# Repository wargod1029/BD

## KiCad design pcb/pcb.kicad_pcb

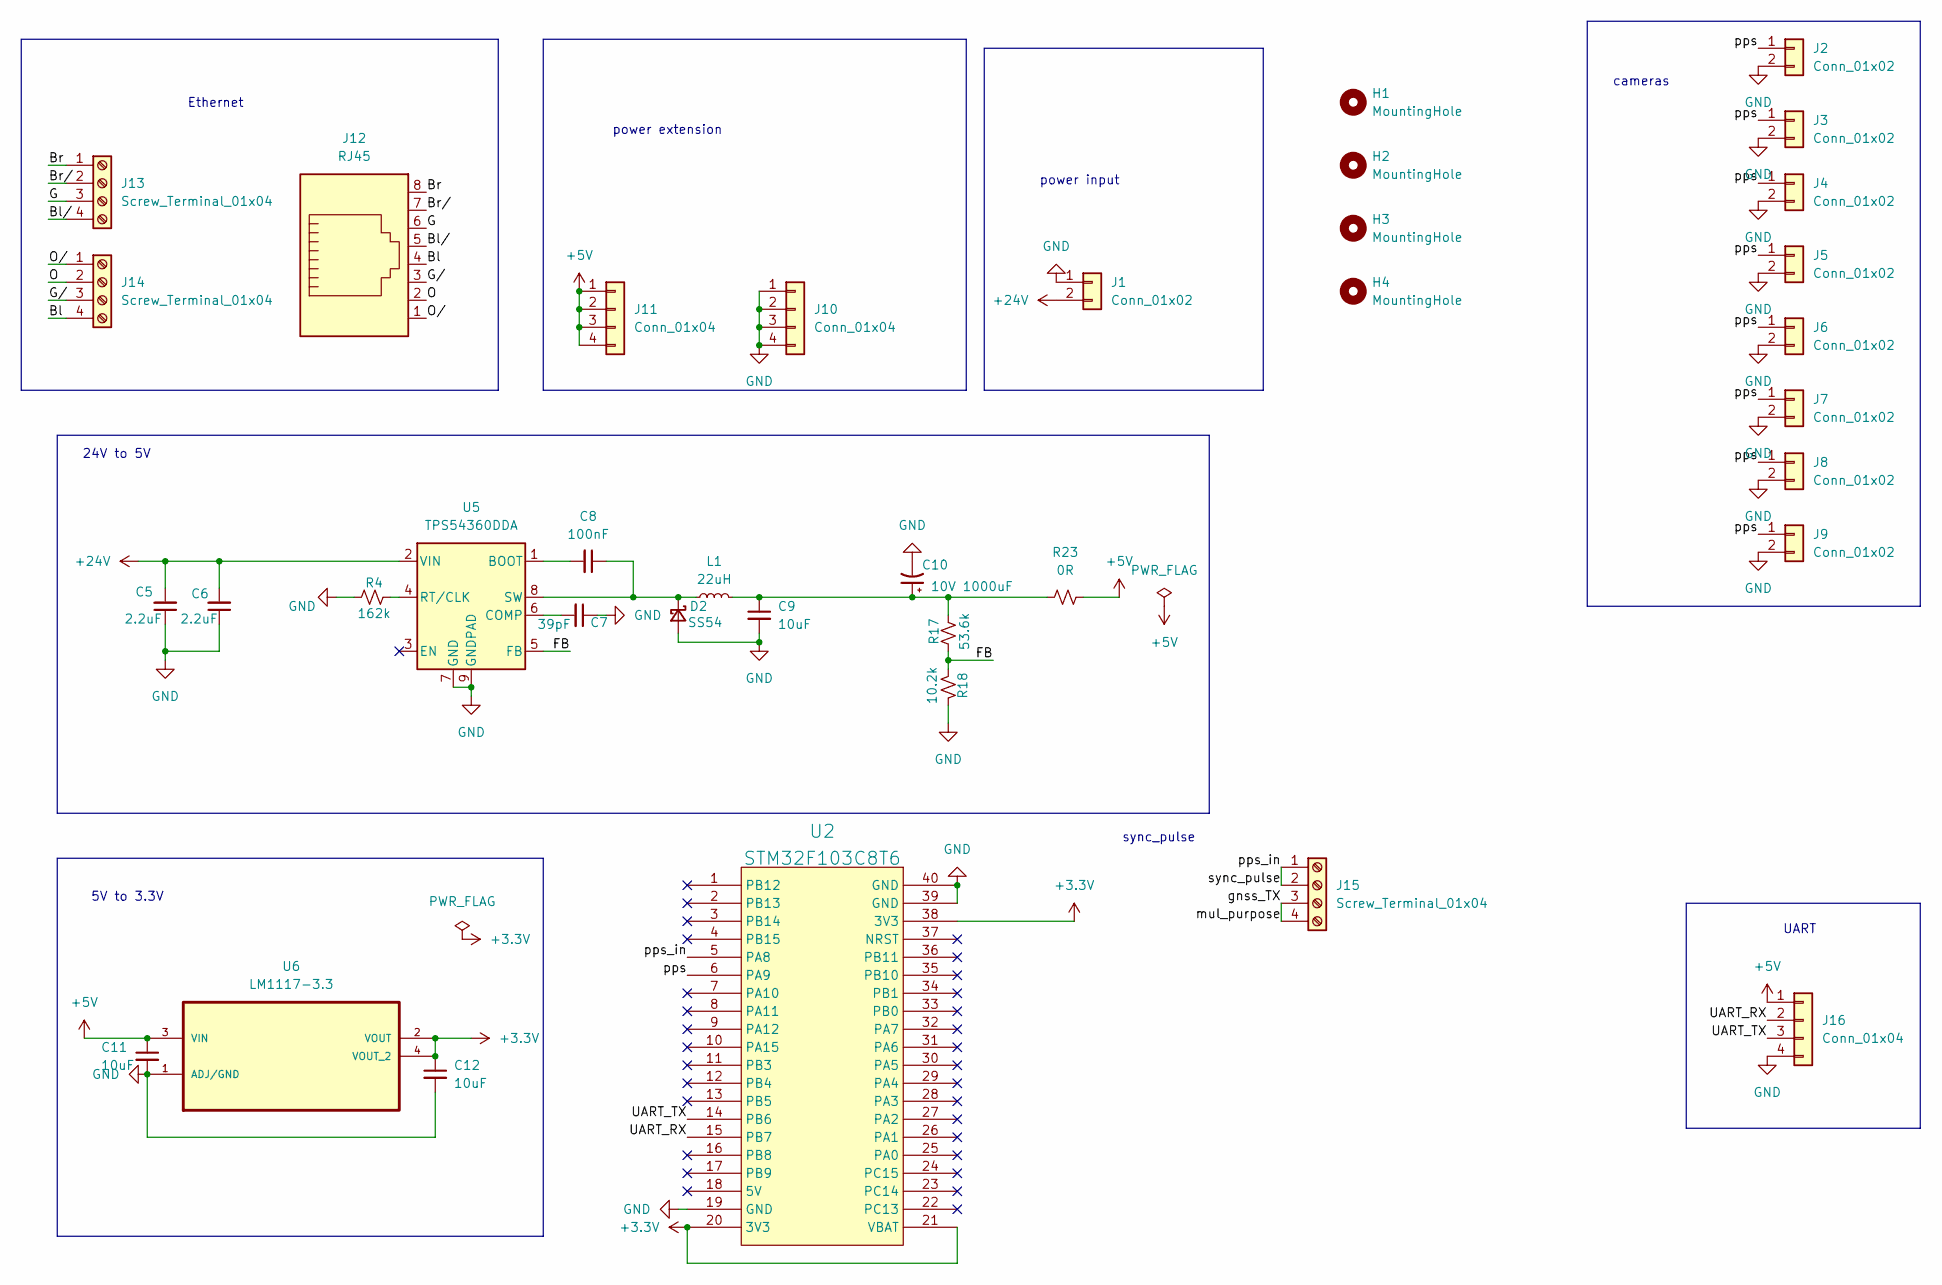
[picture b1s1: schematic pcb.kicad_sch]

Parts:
C5, C6: 2.2uF; C_0603_1608Metric
C7: 39pF; C_0603_1608Metric
C8: 100nF; C_0603_1608Metric
C9, C11, C12: 10uF; C_0603_1608Metric
C10: 10V 1000uF; CP_Radial_D8.0mm_P12.00mm
D2: SS54; D_SMA
H1, H2, H3, H4: MountingHole; MountingHole_3.2mm_M3
J1: Conn_01x02; AMASS_XT30U-M_1x02_P5.0mm_Vertical
J2, J3, J4, J5, J6, J7, J8, J9: Conn_01x02; JST_XH_B2B-XH-A_1x02_P2.50mm_Vertical
J10, J11, J16: Conn_01x04; JST_XH_B4B-XH-A_1x04_P2.50mm_Vertical
J12: RJ45; RJ45_Amphenol_54602-x08_Horizontal
J13, J14, J15: Screw_Terminal_01x04; TerminalBlock_MetzConnect_Type011_RT05504HBLC_1x04_P5.00mm_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
L1: 22uH; L_7.3x7.3_H3.5
R4: 162k; R_0603_1608Metric
R17: 53.6k; R_0603_1608Metric
R18: 10.2k; R_0603_1608Metric
R23: 0R; R_0603_1608Metric
U2: STM32F103C8T6; Stm32 BluePill
U5: TPS54360DDA; TI_SO-PowerPAD-8_ThermalVias
U6: LM1117-3.3; SOT-223

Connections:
+3.3V: C12.1, U2.20 (3V3), U2.21 (VBAT), U2.38 (3V3), U6.2 (VOUT), U6.4 (VOUT_2)
+5V: C11.1, J11.1, J11.2, J11.3, J11.4, J16.1, R23.1, U6.3 (VIN)
+24V: C5.2, C6.2, J1.2, U5.2 (VIN)
/Bl: J12.4, J14.4
/Bl/: J12.5, J13.4
/Br: J12.8, J13.1
/Br/: J12.7, J13.2
/FB: R17.1, R18.2, U5.5 (FB)
/G: J12.6, J13.3
/G/: J12.3, J14.3
/O: J12.2, J14.2
/O/: J12.1, J14.1
/UART_RX: J16.2, U2.15 (PB7)
/UART_TX: J16.3, U2.14 (PB6)
/gnss_TX: J15.3, J15.4
/pps: J2.1, J3.1, J4.1, J5.1, J6.1, J7.1, J8.1, J9.1, U2.6 (PA9)
/pps_in: J15.1, J15.2, U2.5 (PA8)
GND: C5.1, C6.1, C7.1, C9.2, C10.2, C11.2, C12.2, D2.2 (A), J1.1, J2.2, J3.2, J4.2, J5.2, J6.2, J7.2, J8.2, J9.2, J10.1, J10.2, J10.3, J10.4, J16.4, R4.1, R18.1, U2.19 (GND), U2.39 (GND), U2.40 (GND), U5.7 (GND), U5.9 (GNDPAD), U6.1 (ADJ/GND)
unnamed: C9.1, C10.1, L1.2, R17.2, R23.2
unnamed: C8.1, D2.1 (K), L1.1, U5.8 (SW)
unnamed: C8.2, U5.1 (BOOT)
unnamed: C7.2, U5.6 (COMP)
unnamed: R4.2, U5.4 (RT/CLK)

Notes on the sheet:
UART
Ethernet
5V to 3.3V
24V to 5V
power input
power extension
cameras
sync_pulse

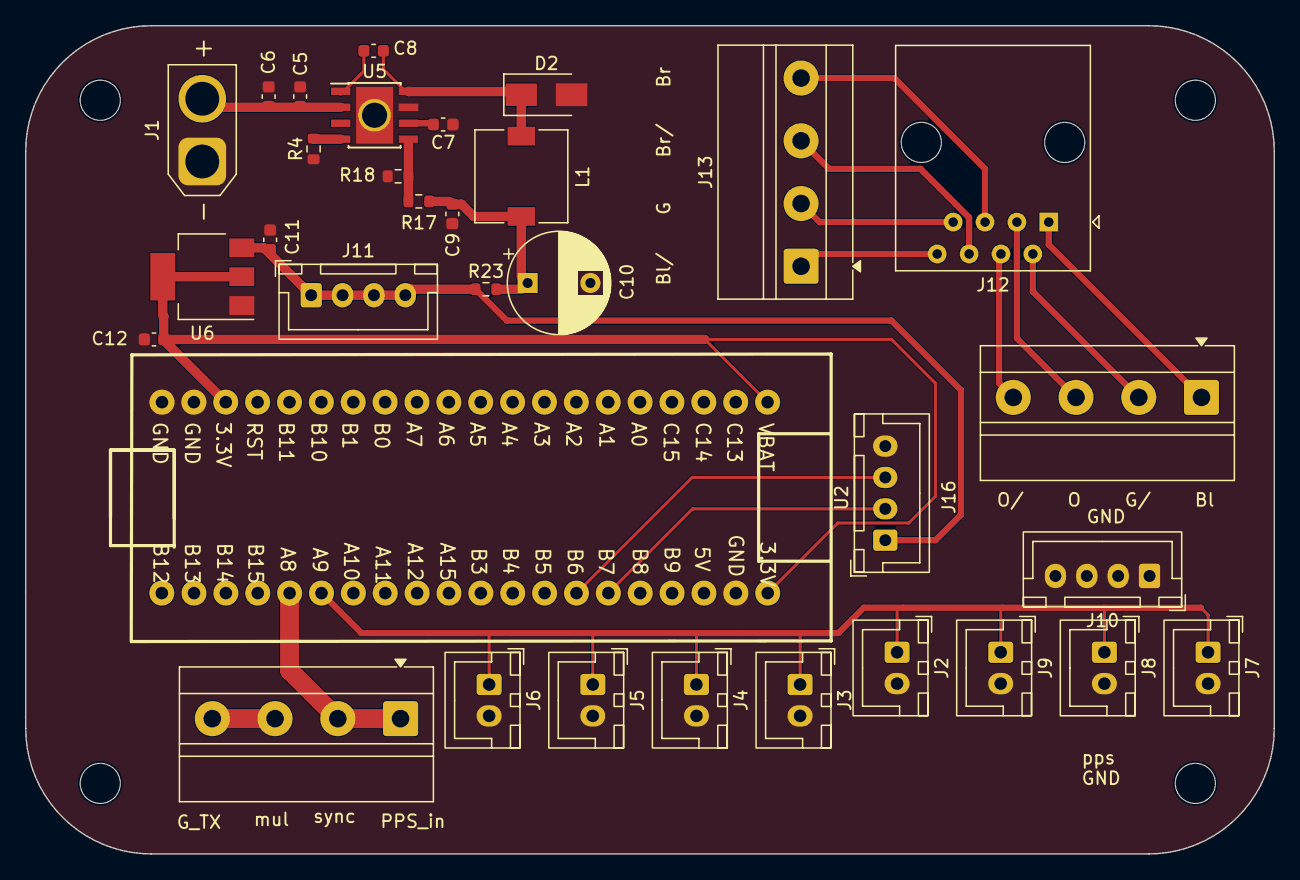
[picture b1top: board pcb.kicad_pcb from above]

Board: 2 copper layers, 99.5 x 66.0 mm, 37 parts (0 on the bottom side), 23 nets.
